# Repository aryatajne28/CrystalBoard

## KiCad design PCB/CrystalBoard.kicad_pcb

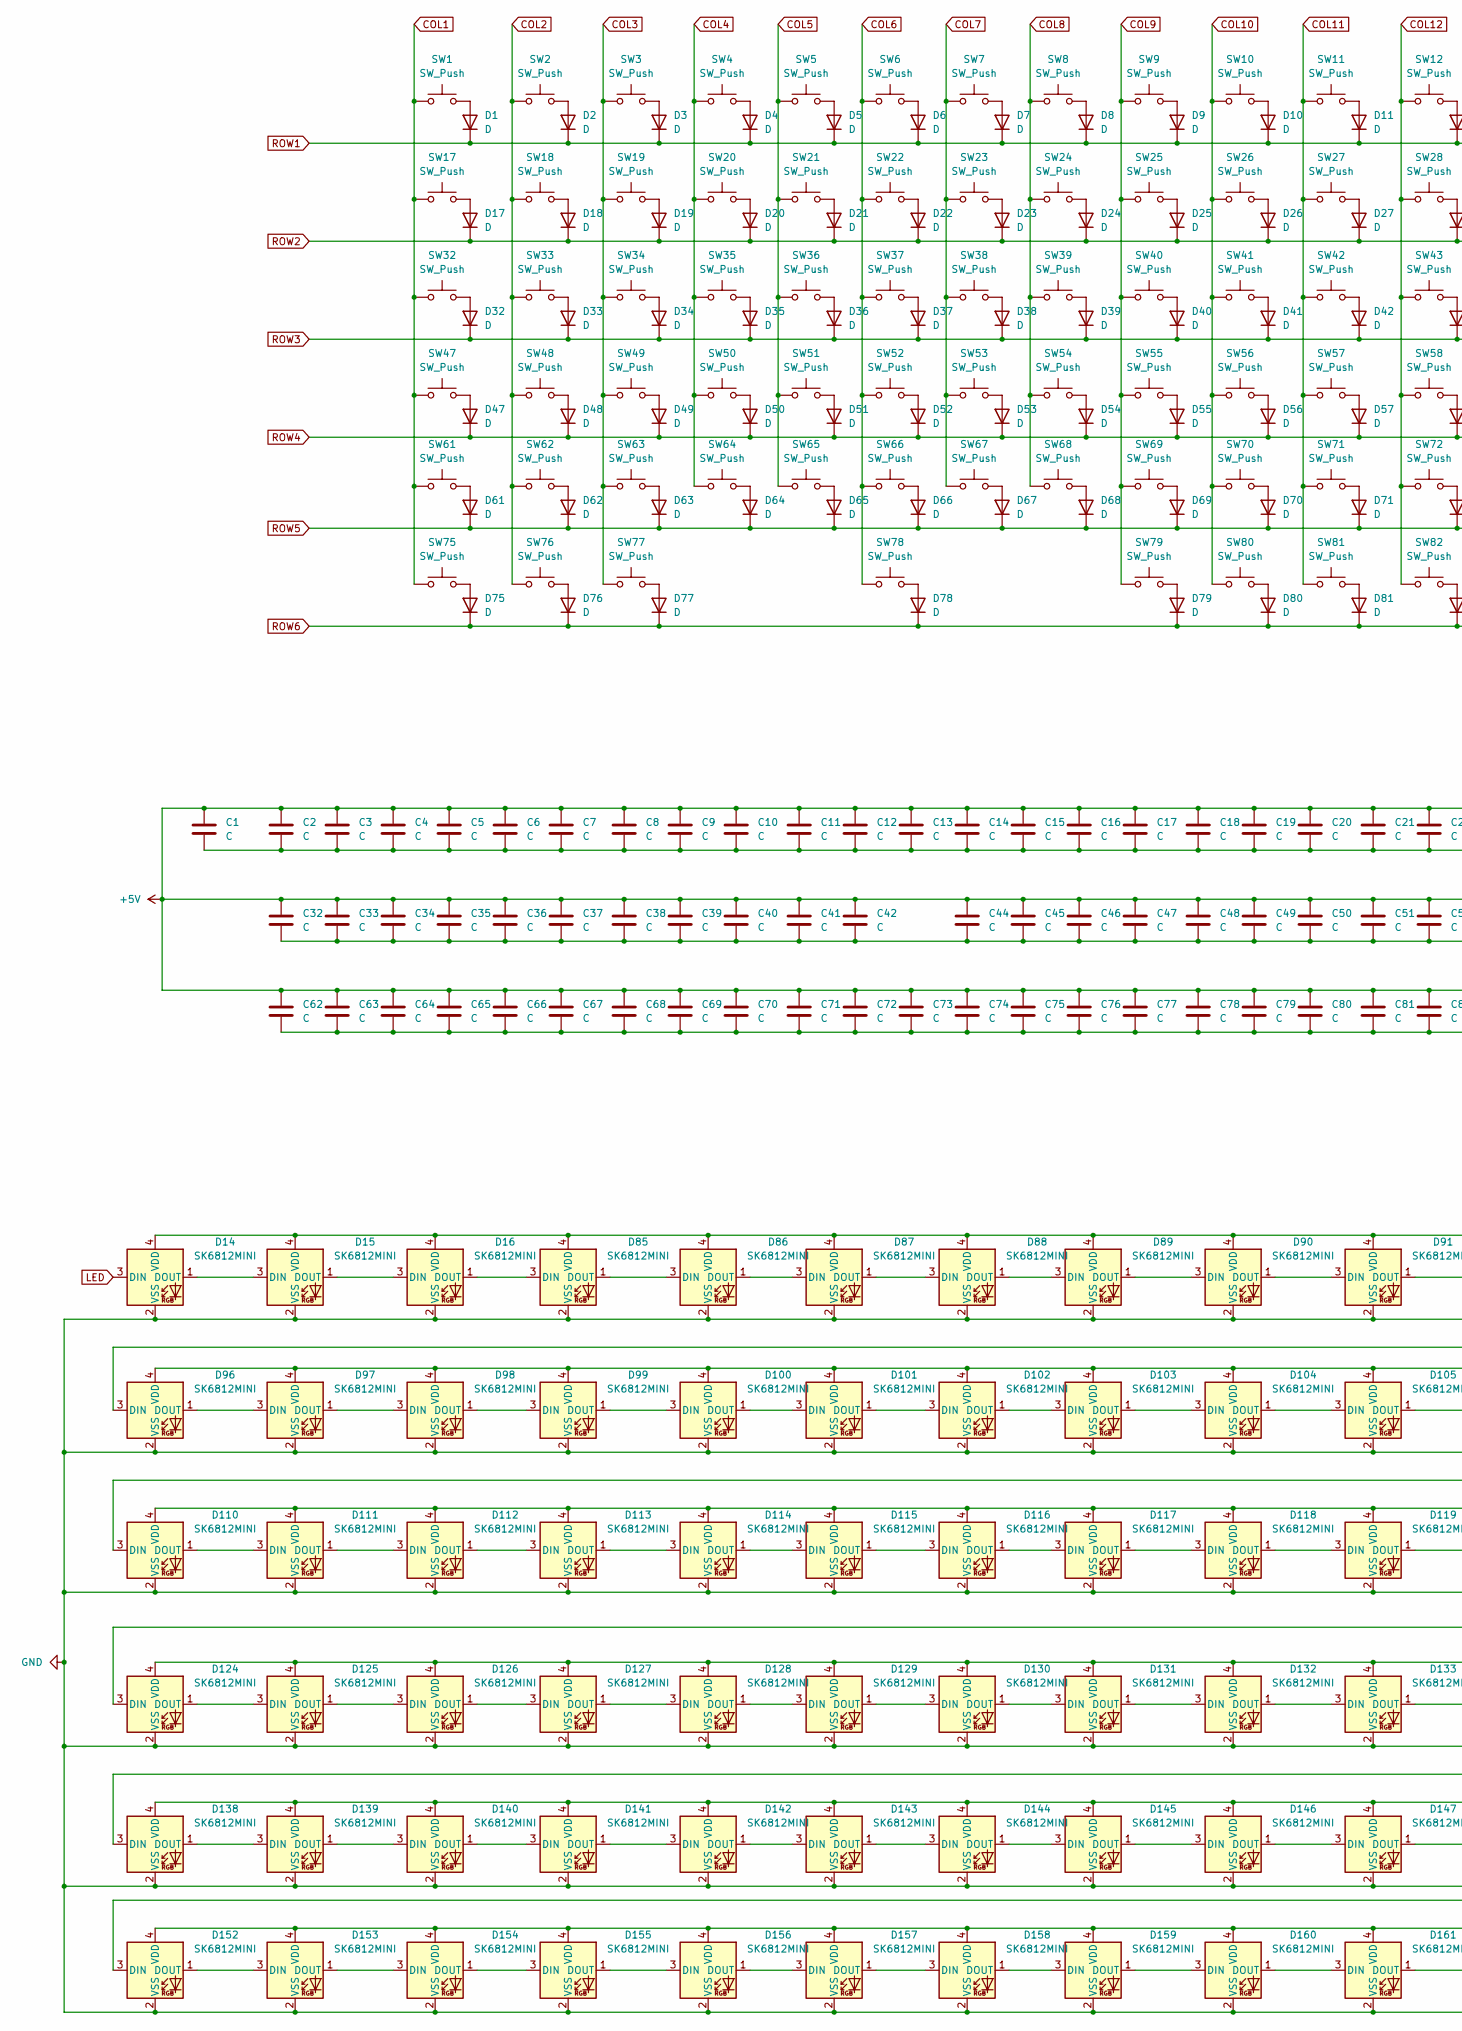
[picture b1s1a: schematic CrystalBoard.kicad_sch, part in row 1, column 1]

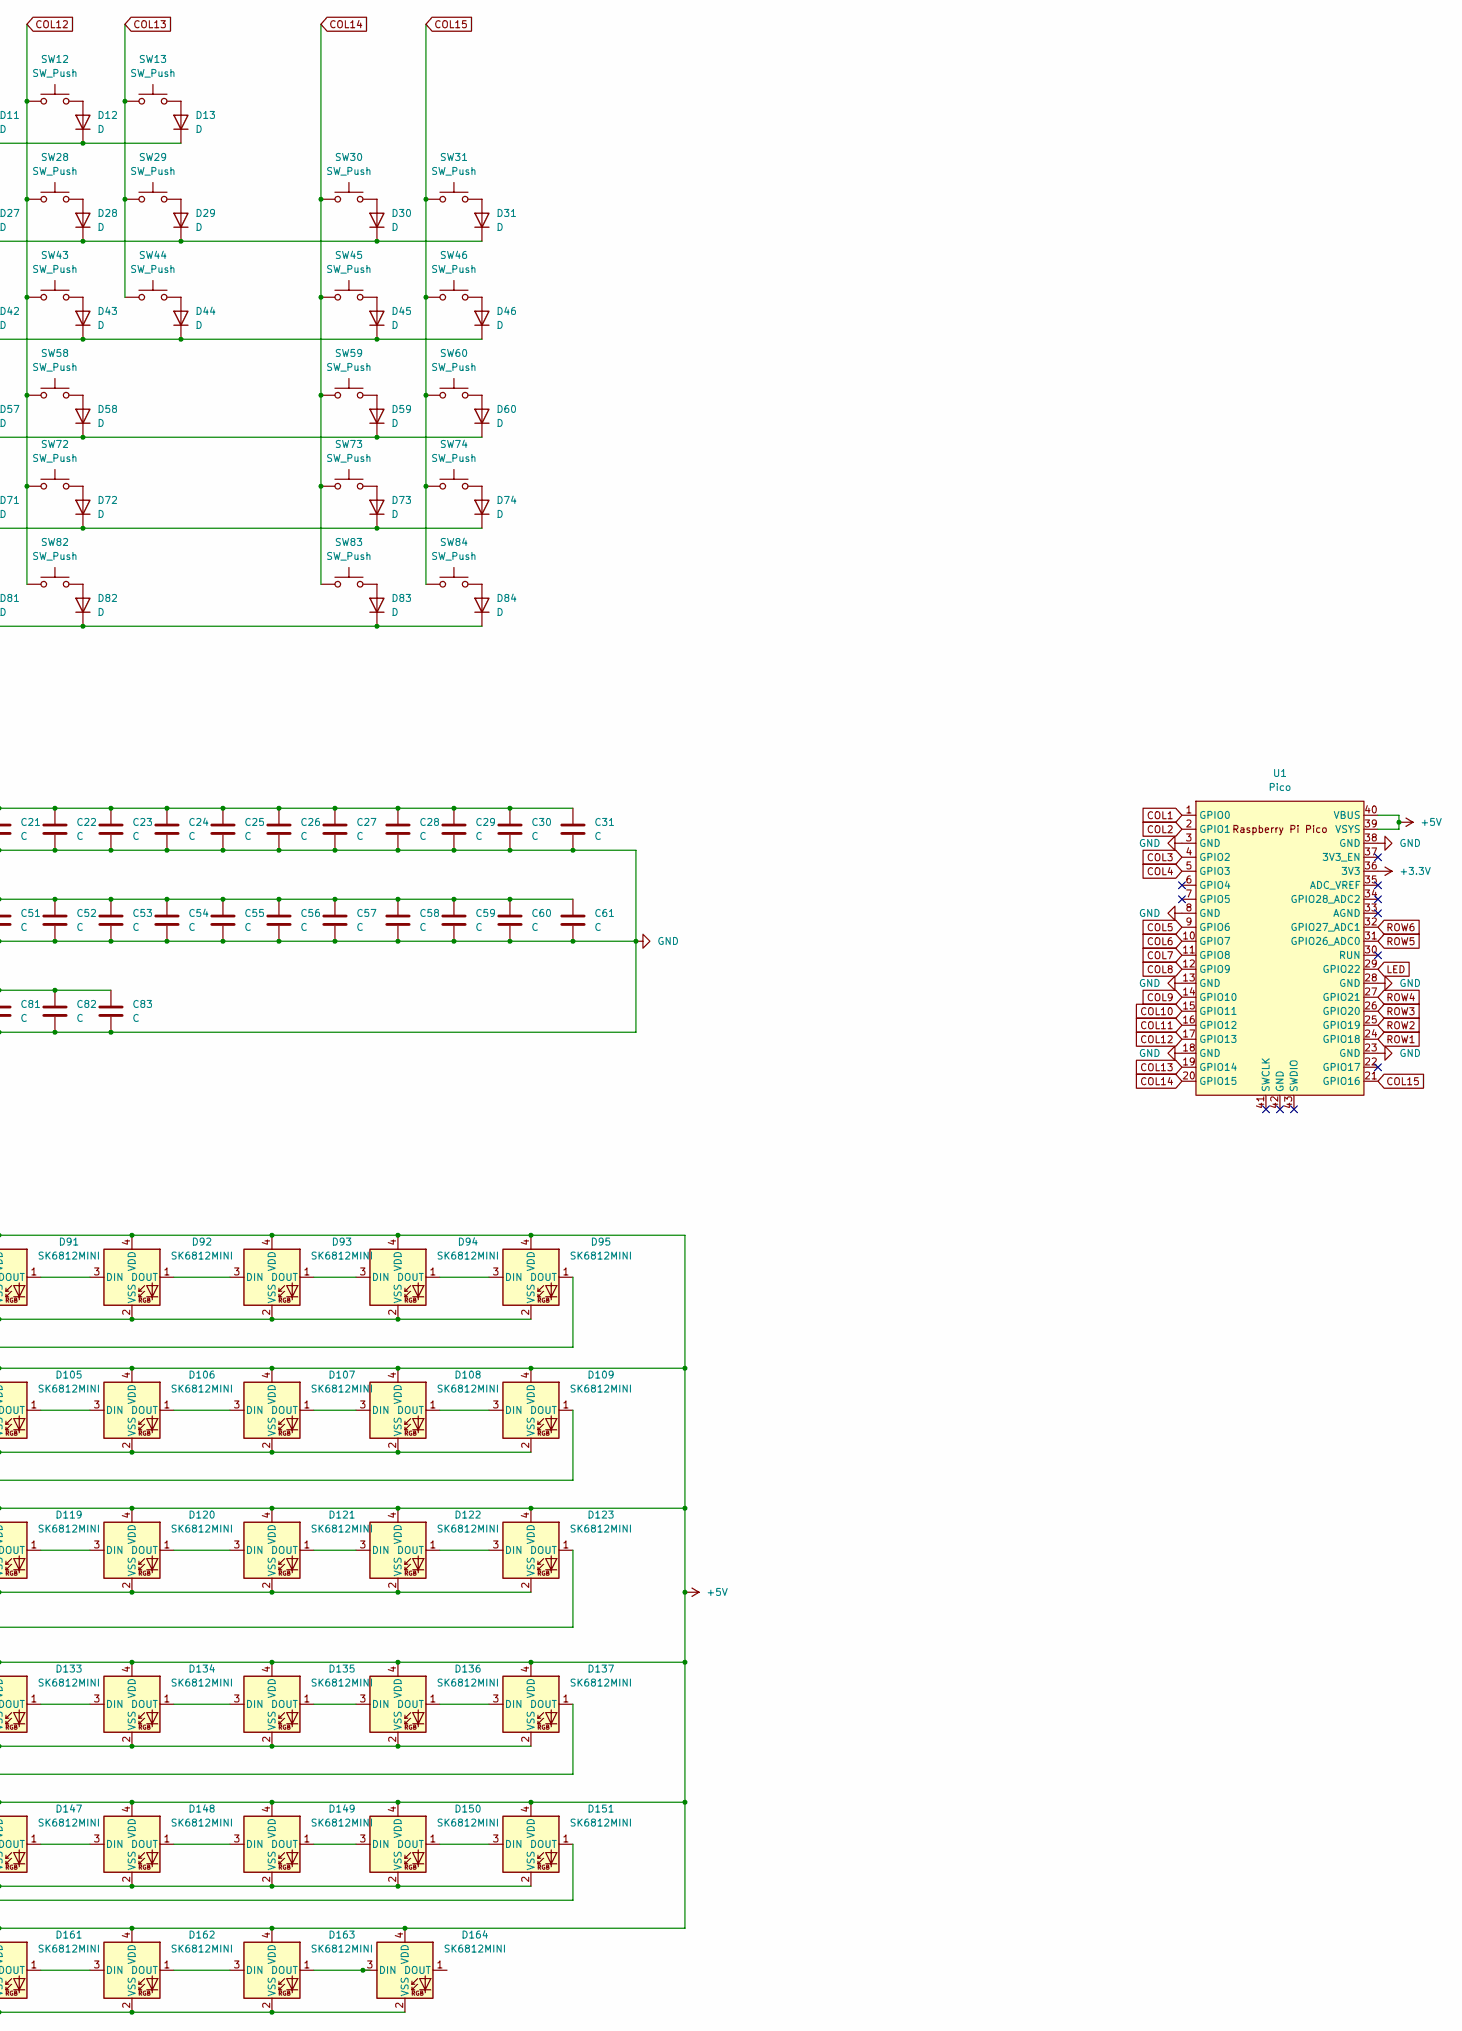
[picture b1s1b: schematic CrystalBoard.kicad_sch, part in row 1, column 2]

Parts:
C1, C2, C3, C4, C5, C6, C7, C8, C9, C10, C11, C12, C13, C14, C15, C16, C17, C18, C19, C20, C21, C22, C23, C24, C25, C26, C27, C28, C29, C30, C31, C32, C33, C34, C35, C36, C37, C38, C39, C40, C41, C42, C44, C45, C46, C47, C48, C49, C50, C51, C52, C53, C54, C55, C56, C57, C58, C59, C60, C61, C62, C63, C64, C65, C66, C67, C68, C69, C70, C71, C72, C73, C74, C75, C76, C77, C78, C79, C80, C81, C82, C83: C; C_0805_2012Metric_Pad1.18x1.45mm_HandSolder
D1, D2, D3, D4, D5, D6, D7, D8, D9, D10, D11, D12, D13, D17, D18, D19, D20, D21, D22, D23, D24, D25, D26, D27, D28, D29, D30, D31, D32, D33, D34, D35, D36, D37, D38, D39, D40, D41, D42, D43, D44, D45, D46, D47, D48, D49, D50, D51, D52, D53, D54, D55, D56, D57, D58, D59, D60, D61, D62, D63, D64, D65, D66, D67, D68, D69, D70, D71, D72, D73, D74, D75, D76, D77, D78, D79, D80, D81, D82, D83, D84: D; D_DO-35_SOD27_P7.62mm_Horizontal
D14, D15, D16, D85, D86, D87, D88, D89, D90, D91, D92, D93, D94, D95, D96, D97, D98, D99, D100, D101, D102, D103, D104, D105, D106, D107, D108, D109, D110, D111, D112, D113, D114, D115, D116, D117, D118, D119, D120, D121, D122, D123, D124, D125, D126, D127, D128, D129, D130, D131, D132, D133, D134, D135, D136, D137, D138, D139, D140, D141, D142, D143, D144, D145, D146, D147, D148, D149, D150, D151, D152, D153, D154, D155, D156, D157, D158, D159, D160, D161, D162, D163, D164: SK6812MINI; SK6812-MINI-E
SW1, SW2, SW3, SW4, SW5, SW6, SW7, SW8, SW9, SW10, SW11, SW12, SW13, SW17, SW18, SW19, SW20, SW21, SW22, SW23, SW24, SW25, SW26, SW27, SW28, SW29, SW31, SW33, SW34, SW35, SW36, SW37, SW38, SW39, SW40, SW41, SW42, SW43, SW44, SW46, SW48, SW49, SW50, SW51, SW52, SW53, SW54, SW55, SW56, SW57, SW58, SW60, SW62, SW63, SW64, SW65, SW66, SW67, SW68, SW69, SW70, SW71, SW73, SW74, SW79, SW80, SW81, SW82, SW83, SW84: SW_Push; SW_Cherry_MX_PCB_1.00u
SW30: SW_Push; SW_Cherry_MX_PCB_2.00u
SW32, SW45: SW_Push; SW_Cherry_MX_PCB_1.50u
SW47, SW72: SW_Push; SW_Cherry_MX_PCB_1.75u
SW59, SW61: SW_Push; SW_Cherry_MX_PCB_2.25u
SW75, SW76, SW77: SW_Push; SW_Cherry_MX_PCB_1.25u
SW78: SW_Push; SW_Cherry_MX_PCB_6.25u
U1: Pico; RPi_Pico_SMD_TH

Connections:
+3.3V: U1.36 (3V3)
+5V: C1.1, C2.1, C3.1, C4.1, C5.1, C6.1, C7.1, C8.1, C9.1, C10.1, C11.1, C12.1, C13.1, C14.1, C15.1, C16.1, C17.1, C18.1, C19.1, C20.1, C21.1, C22.1, C23.1, C24.1, C25.1, C26.1, C27.1, C28.1, C29.1, C30.1, C31.1, C32.1, C33.1, C34.1, C35.1, C36.1, C37.1, C38.1, C39.1, C40.1, C41.1, C42.1, C44.1, C45.1, C46.1, C47.1, C48.1, C49.1, C50.1, C51.1, C52.1, C53.1, C54.1, C55.1, C56.1, C57.1, C58.1, C59.1, C60.1, C61.1, C62.1, C63.1, C64.1, C65.1, C66.1, C67.1, C68.1, C69.1, C70.1, C71.1, C72.1, C73.1, C74.1, C75.1, C76.1, C77.1, C78.1, C79.1, C80.1, C81.1, C82.1, C83.1, D14.4 (VDD), D15.4 (VDD), D16.4 (VDD), D85.4 (VDD), D86.4 (VDD), D87.4 (VDD), D88.4 (VDD), D89.4 (VDD), D90.4 (VDD), D91.4 (VDD), D92.4 (VDD), D93.4 (VDD), D94.4 (VDD), D95.4 (VDD), D96.4 (VDD), D97.4 (VDD), D98.4 (VDD), D99.4 (VDD), D100.4 (VDD), D101.4 (VDD), D102.4 (VDD), D103.4 (VDD), D104.4 (VDD), D105.4 (VDD), D106.4 (VDD), D107.4 (VDD), D108.4 (VDD), D109.4 (VDD), D110.4 (VDD), D111.4 (VDD), D112.4 (VDD), D113.4 (VDD), D114.4 (VDD), D115.4 (VDD), D116.4 (VDD), D117.4 (VDD), D118.4 (VDD), D119.4 (VDD), D120.4 (VDD), D121.4 (VDD), D122.4 (VDD), D123.4 (VDD), D124.4 (VDD), D125.4 (VDD), D126.4 (VDD), D127.4 (VDD), D128.4 (VDD), D129.4 (VDD), D130.4 (VDD), D131.4 (VDD), D132.4 (VDD), D133.4 (VDD), D134.4 (VDD), D135.4 (VDD), D136.4 (VDD), D137.4 (VDD), D138.4 (VDD), D139.4 (VDD), D140.4 (VDD), D141.4 (VDD), D142.4 (VDD), D143.4 (VDD), D144.4 (VDD), D145.4 (VDD), D146.4 (VDD), D147.4 (VDD), D148.4 (VDD), D149.4 (VDD), D150.4 (VDD), D151.4 (VDD), D152.4 (VDD), D153.4 (VDD), D154.4 (VDD), D155.4 (VDD), D156.4 (VDD), D157.4 (VDD), D158.4 (VDD), D159.4 (VDD), D160.4 (VDD), D161.4 (VDD), D162.4 (VDD), D163.4 (VDD), D164.4 (VDD), U1.39 (VSYS), U1.40 (VBUS); also elsewhere on the board
COL1: SW1.1, SW17.1, SW32.1, SW47.1, SW61.1, SW75.1, U1.1 (GPIO0)
COL2: SW2.1, SW18.1, SW33.1, SW48.1, SW62.1, SW76.1, U1.2 (GPIO1)
COL3: SW3.1, SW19.1, SW34.1, SW49.1, SW63.1, SW77.1, U1.4 (GPIO2)
COL4: SW4.1, SW20.1, SW35.1, SW50.1, SW64.1, U1.5 (GPIO3)
COL5: SW5.1, SW21.1, SW36.1, SW51.1, SW65.1, U1.9 (GPIO6)
COL6: SW6.1, SW22.1, SW37.1, SW52.1, SW66.1, SW78.1, U1.10 (GPIO7)
COL7: SW7.1, SW23.1, SW38.1, SW53.1, SW67.1, U1.11 (GPIO8)
COL8: SW8.1, SW24.1, SW39.1, SW54.1, SW68.1, U1.12 (GPIO9)
COL9: SW9.1, SW25.1, SW40.1, SW55.1, SW69.1, SW79.1, U1.14 (GPIO10)
COL10: SW10.1, SW26.1, SW41.1, SW56.1, SW70.1, SW80.1, U1.15 (GPIO11)
COL11: SW11.1, SW27.1, SW42.1, SW57.1, SW71.1, SW81.1, U1.16 (GPIO12)
COL12: SW12.1, SW28.1, SW43.1, SW58.1, SW72.1, SW82.1, U1.17 (GPIO13)
COL13: SW13.1, SW29.1, SW44.1, U1.19 (GPIO14)
COL14: SW30.1, SW45.1, SW59.1, SW73.1, SW83.1, U1.20 (GPIO15)
COL15: SW31.1, SW46.1, SW60.1, SW74.1, SW84.1, U1.21 (GPIO16)
GND: C1.2, C2.2, C3.2, C4.2, C5.2, C6.2, C7.2, C8.2, C9.2, C10.2, C11.2, C12.2, C13.2, C14.2, C15.2, C16.2, C17.2, C18.2, C19.2, C20.2, C21.2, C22.2, C23.2, C24.2, C25.2, C26.2, C27.2, C28.2, C29.2, C30.2, C31.2, C32.2, C33.2, C34.2, C35.2, C36.2, C37.2, C38.2, C39.2, C40.2, C41.2, C42.2, C44.2, C45.2, C46.2, C47.2, C48.2, C49.2, C50.2, C51.2, C52.2, C53.2, C54.2, C55.2, C56.2, C57.2, C58.2, C59.2, C60.2, C61.2, C62.2, C63.2, C64.2, C65.2, C66.2, C67.2, C68.2, C69.2, C70.2, C71.2, C72.2, C73.2, C74.2, C75.2, C76.2, C77.2, C78.2, C79.2, C80.2, C81.2, C82.2, C83.2, D14.2 (VSS), D15.2 (VSS), D16.2 (VSS), D85.2 (VSS), D86.2 (VSS), D87.2 (VSS), D88.2 (VSS), D89.2 (VSS), D90.2 (VSS), D91.2 (VSS), D92.2 (VSS), D93.2 (VSS), D94.2 (VSS), D95.2 (VSS), D96.2 (VSS), D97.2 (VSS), D98.2 (VSS), D99.2 (VSS), D100.2 (VSS), D101.2 (VSS), D102.2 (VSS), D103.2 (VSS), D104.2 (VSS), D105.2 (VSS), D106.2 (VSS), D107.2 (VSS), D108.2 (VSS), D109.2 (VSS), D110.2 (VSS), D111.2 (VSS), D112.2 (VSS), D113.2 (VSS), D114.2 (VSS), D115.2 (VSS), D116.2 (VSS), D117.2 (VSS), D118.2 (VSS), D119.2 (VSS), D120.2 (VSS), D121.2 (VSS), D122.2 (VSS), D123.2 (VSS), D124.2 (VSS), D125.2 (VSS), D126.2 (VSS), D127.2 (VSS), D128.2 (VSS), D129.2 (VSS), D130.2 (VSS), D131.2 (VSS), D132.2 (VSS), D133.2 (VSS), D134.2 (VSS), D135.2 (VSS), D136.2 (VSS), D137.2 (VSS), D138.2 (VSS), D139.2 (VSS), D140.2 (VSS), D141.2 (VSS), D142.2 (VSS), D143.2 (VSS), D144.2 (VSS), D145.2 (VSS), D146.2 (VSS), D147.2 (VSS), D148.2 (VSS), D149.2 (VSS), D150.2 (VSS), D151.2 (VSS), D152.2 (VSS), D153.2 (VSS), D154.2 (VSS), D155.2 (VSS), D156.2 (VSS), D157.2 (VSS), D158.2 (VSS), D159.2 (VSS), D160.2 (VSS), D161.2 (VSS), D162.2 (VSS), D163.2 (VSS), D164.2 (VSS), U1.3 (GND), U1.8 (GND), U1.13 (GND), U1.18 (GND), U1.23 (GND), U1.28 (GND), U1.38 (GND); also elsewhere on the board
LED: D14.3 (DIN), U1.29 (GPIO22)
unnamed: D1.2 (A), SW1.2
unnamed: D2.2 (A), SW2.2
unnamed: D3.2 (A), SW3.2
unnamed: D4.2 (A), SW4.2
unnamed: D5.2 (A), SW5.2
unnamed: D6.2 (A), SW6.2
unnamed: D7.2 (A), SW7.2
unnamed: D8.2 (A), SW8.2
unnamed: D9.2 (A), SW9.2
unnamed: D10.2 (A), SW10.2
unnamed: D11.2 (A), SW11.2
unnamed: D12.2 (A), SW12.2
unnamed: D13.2 (A), SW13.2
unnamed: D14.1 (DOUT), D15.3 (DIN)
unnamed: D15.1 (DOUT), D16.3 (DIN)
unnamed: D16.1 (DOUT), D85.3 (DIN)
unnamed: D17.2 (A), SW17.2
unnamed: D18.2 (A), SW18.2
unnamed: D19.2 (A), SW19.2
unnamed: D20.2 (A), SW20.2
unnamed: D21.2 (A), SW21.2
unnamed: D22.2 (A), SW22.2
unnamed: D23.2 (A), SW23.2
unnamed: D24.2 (A), SW24.2
unnamed: D25.2 (A), SW25.2
unnamed: D26.2 (A), SW26.2
unnamed: D27.2 (A), SW27.2
unnamed: D28.2 (A), SW28.2
unnamed: D29.2 (A), SW29.2
unnamed: D30.2 (A), SW30.2
unnamed: D31.2 (A), SW31.2
unnamed: D32.2 (A), SW32.2
unnamed: D33.2 (A), SW33.2
unnamed: D34.2 (A), SW34.2
unnamed: D35.2 (A), SW35.2
unnamed: D36.2 (A), SW36.2
unnamed: D37.2 (A), SW37.2
unnamed: D38.2 (A), SW38.2
unnamed: D39.2 (A), SW39.2
unnamed: D40.2 (A), SW40.2
unnamed: D41.2 (A), SW41.2
unnamed: D42.2 (A), SW42.2
unnamed: D43.2 (A), SW43.2
unnamed: D44.2 (A), SW44.2
unnamed: D45.2 (A), SW45.2
unnamed: D46.2 (A), SW46.2
unnamed: D47.2 (A), SW47.2
unnamed: D48.2 (A), SW48.2
unnamed: D49.2 (A), SW49.2
unnamed: D50.2 (A), SW50.2
unnamed: D51.2 (A), SW51.2
unnamed: D52.2 (A), SW52.2
unnamed: D53.2 (A), SW53.2
unnamed: D54.2 (A), SW54.2
unnamed: D55.2 (A), SW55.2
unnamed: D56.2 (A), SW56.2
unnamed: D57.2 (A), SW57.2
unnamed: D58.2 (A), SW58.2
unnamed: D59.2 (A), SW59.2
unnamed: D60.2 (A), SW60.2
unnamed: D61.2 (A), SW61.2
unnamed: D62.2 (A), SW62.2
unnamed: D63.2 (A), SW63.2
unnamed: D64.2 (A), SW64.2
unnamed: D65.2 (A), SW65.2
unnamed: D66.2 (A), SW66.2
unnamed: D67.2 (A), SW67.2
unnamed: D68.2 (A), SW68.2
unnamed: D69.2 (A), SW69.2
unnamed: D70.2 (A), SW70.2
unnamed: D71.2 (A), SW71.2
unnamed: D72.2 (A), SW72.2
unnamed: D73.2 (A), SW73.2
unnamed: D74.2 (A), SW74.2
unnamed: D75.2 (A), SW75.2
unnamed: D76.2 (A), SW76.2
unnamed: D77.2 (A), SW77.2
unnamed: D78.2 (A), SW78.2
unnamed: D79.2 (A), SW79.2
unnamed: D80.2 (A), SW80.2
unnamed: D81.2 (A), SW81.2
unnamed: D82.2 (A), SW82.2
unnamed: D83.2 (A), SW83.2
unnamed: D84.2 (A), SW84.2
unnamed: D85.1 (DOUT), D86.3 (DIN)
unnamed: D86.1 (DOUT), D87.3 (DIN)
unnamed: D87.1 (DOUT), D88.3 (DIN)
unnamed: D88.1 (DOUT), D89.3 (DIN)
unnamed: D89.1 (DOUT), D90.3 (DIN)
unnamed: D90.1 (DOUT), D91.3 (DIN)
unnamed: D91.1 (DOUT), D92.3 (DIN)
unnamed: D92.1 (DOUT), D93.3 (DIN)
unnamed: D93.1 (DOUT), D94.3 (DIN)
unnamed: D94.1 (DOUT), D95.3 (DIN)
unnamed: D95.1 (DOUT), D96.3 (DIN)
unnamed: D96.1 (DOUT), D97.3 (DIN)
unnamed: D97.1 (DOUT), D98.3 (DIN)
unnamed: D98.1 (DOUT), D99.3 (DIN)
unnamed: D99.1 (DOUT), D100.3 (DIN)
unnamed: D100.1 (DOUT), D101.3 (DIN)
unnamed: D101.1 (DOUT), D102.3 (DIN)
unnamed: D102.1 (DOUT), D103.3 (DIN)
unnamed: D103.1 (DOUT), D104.3 (DIN)
unnamed: D104.1 (DOUT), D105.3 (DIN)
unnamed: D105.1 (DOUT), D106.3 (DIN)
unnamed: D106.1 (DOUT), D107.3 (DIN)
unnamed: D107.1 (DOUT), D108.3 (DIN)
unnamed: D108.1 (DOUT), D109.3 (DIN)
unnamed: D109.1 (DOUT), D110.3 (DIN)
unnamed: D110.1 (DOUT), D111.3 (DIN)
unnamed: D111.1 (DOUT), D112.3 (DIN)
unnamed: D112.1 (DOUT), D113.3 (DIN)
unnamed: D113.1 (DOUT), D114.3 (DIN)
unnamed: D114.1 (DOUT), D115.3 (DIN)
unnamed: D115.1 (DOUT), D116.3 (DIN)
unnamed: D116.1 (DOUT), D117.3 (DIN)
unnamed: D117.1 (DOUT), D118.3 (DIN)
unnamed: D118.1 (DOUT), D119.3 (DIN)
unnamed: D119.1 (DOUT), D120.3 (DIN)
unnamed: D120.1 (DOUT), D121.3 (DIN)
unnamed: D121.1 (DOUT), D122.3 (DIN)
unnamed: D122.1 (DOUT), D123.3 (DIN)
unnamed: D123.1 (DOUT), D124.3 (DIN)
unnamed: D124.1 (DOUT), D125.3 (DIN)
unnamed: D125.1 (DOUT), D126.3 (DIN)
unnamed: D126.1 (DOUT), D127.3 (DIN)
unnamed: D127.1 (DOUT), D128.3 (DIN)
unnamed: D128.1 (DOUT), D129.3 (DIN)
unnamed: D129.1 (DOUT), D130.3 (DIN)
unnamed: D130.1 (DOUT), D131.3 (DIN)
unnamed: D131.1 (DOUT), D132.3 (DIN)
unnamed: D132.1 (DOUT), D133.3 (DIN)
unnamed: D133.1 (DOUT), D134.3 (DIN)
unnamed: D134.1 (DOUT), D135.3 (DIN)
unnamed: D135.1 (DOUT), D136.3 (DIN)
unnamed: D136.1 (DOUT), D137.3 (DIN)
unnamed: D137.1 (DOUT), D138.3 (DIN)
unnamed: D138.1 (DOUT), D139.3 (DIN)
unnamed: D139.1 (DOUT), D140.3 (DIN)
unnamed: D140.1 (DOUT), D141.3 (DIN)
unnamed: D141.1 (DOUT), D142.3 (DIN)
unnamed: D142.1 (DOUT), D143.3 (DIN)
unnamed: D143.1 (DOUT), D144.3 (DIN)
unnamed: D144.1 (DOUT), D145.3 (DIN)
unnamed: D145.1 (DOUT), D146.3 (DIN)
unnamed: D146.1 (DOUT), D147.3 (DIN)
unnamed: D147.1 (DOUT), D148.3 (DIN)
unnamed: D148.1 (DOUT), D149.3 (DIN)
unnamed: D149.1 (DOUT), D150.3 (DIN)
unnamed: D150.1 (DOUT), D151.3 (DIN)
unnamed: D151.1 (DOUT), D152.3 (DIN)
unnamed: D152.1 (DOUT), D153.3 (DIN)
unnamed: D153.1 (DOUT), D154.3 (DIN)
unnamed: D154.1 (DOUT), D155.3 (DIN)
unnamed: D155.1 (DOUT), D156.3 (DIN)
unnamed: D156.1 (DOUT), D157.3 (DIN)
unnamed: D157.1 (DOUT), D158.3 (DIN)
unnamed: D158.1 (DOUT), D159.3 (DIN)
unnamed: D159.1 (DOUT), D160.3 (DIN)
unnamed: D160.1 (DOUT), D161.3 (DIN)
unnamed: D161.1 (DOUT), D162.3 (DIN)
unnamed: D162.1 (DOUT), D163.3 (DIN)
unnamed: D163.1 (DOUT), D164.3 (DIN)
ROW1: D1.1 (K), D2.1 (K), D3.1 (K), D4.1 (K), D5.1 (K), D6.1 (K), D7.1 (K), D8.1 (K), D9.1 (K), D10.1 (K), D11.1 (K), D12.1 (K), D13.1 (K), U1.24 (GPIO18)
ROW2: D17.1 (K), D18.1 (K), D19.1 (K), D20.1 (K), D21.1 (K), D22.1 (K), D23.1 (K), D24.1 (K), D25.1 (K), D26.1 (K), D27.1 (K), D28.1 (K), D29.1 (K), D30.1 (K), D31.1 (K), U1.25 (GPIO19)
ROW3: D32.1 (K), D33.1 (K), D34.1 (K), D35.1 (K), D36.1 (K), D37.1 (K), D38.1 (K), D39.1 (K), D40.1 (K), D41.1 (K), D42.1 (K), D43.1 (K), D44.1 (K), D45.1 (K), D46.1 (K), U1.26 (GPIO20)
ROW4: D47.1 (K), D48.1 (K), D49.1 (K), D50.1 (K), D51.1 (K), D52.1 (K), D53.1 (K), D54.1 (K), D55.1 (K), D56.1 (K), D57.1 (K), D58.1 (K), D59.1 (K), D60.1 (K), U1.27 (GPIO21)
ROW5: D61.1 (K), D62.1 (K), D63.1 (K), D64.1 (K), D65.1 (K), D66.1 (K), D67.1 (K), D68.1 (K), D69.1 (K), D70.1 (K), D71.1 (K), D72.1 (K), D73.1 (K), D74.1 (K), U1.31 (GPIO26_ADC0)
ROW6: D75.1 (K), D76.1 (K), D77.1 (K), D78.1 (K), D79.1 (K), D80.1 (K), D81.1 (K), D82.1 (K), D83.1 (K), D84.1 (K), U1.32 (GPIO27_ADC1)

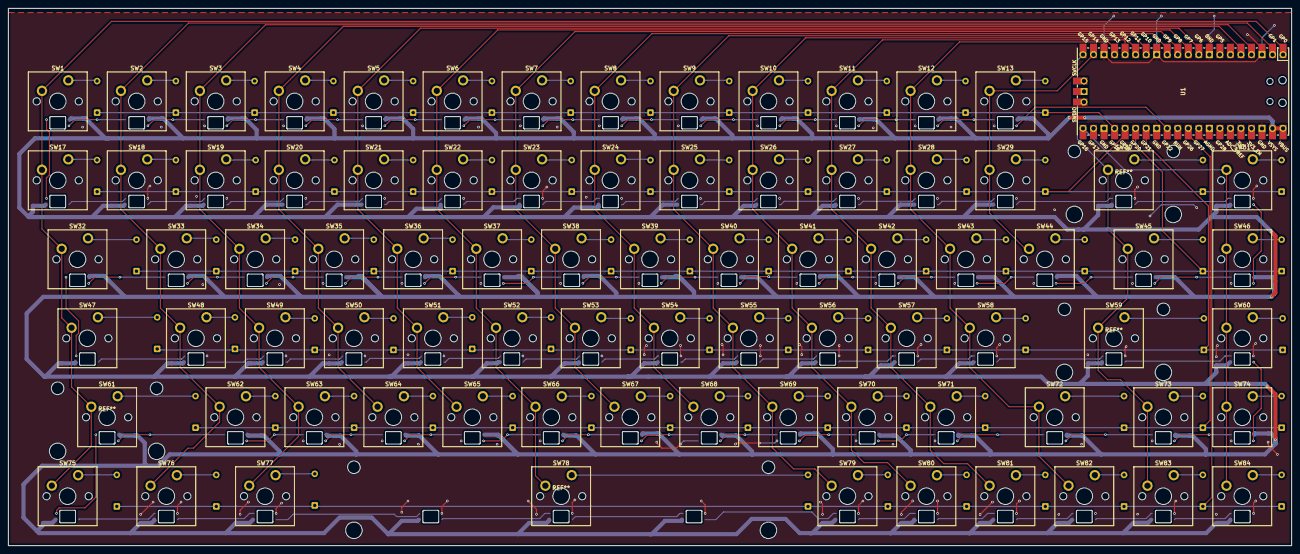
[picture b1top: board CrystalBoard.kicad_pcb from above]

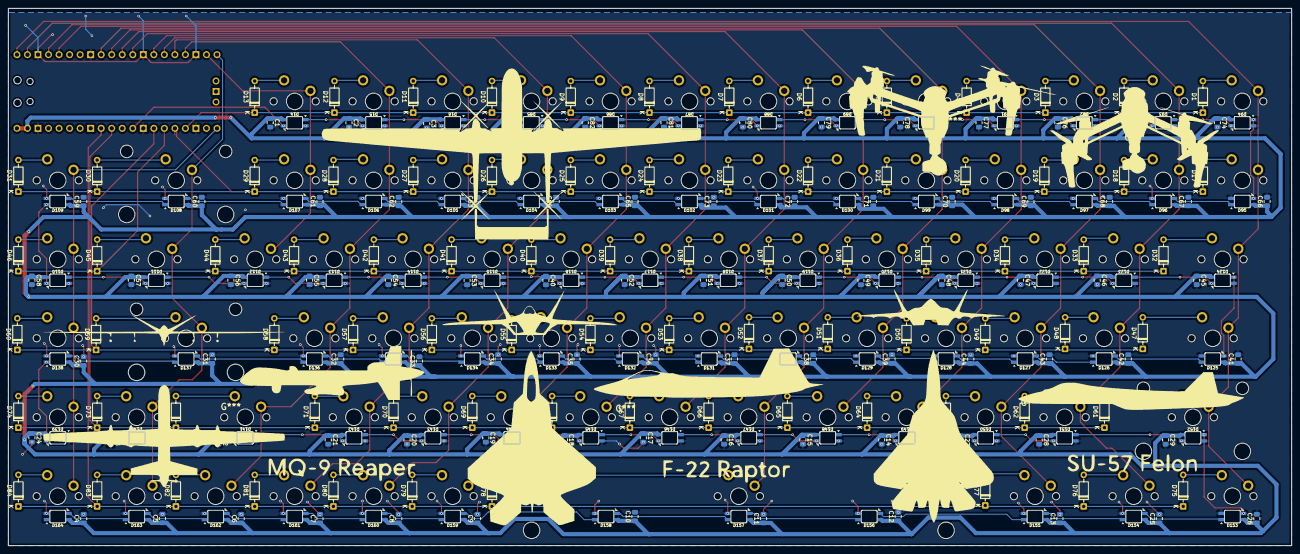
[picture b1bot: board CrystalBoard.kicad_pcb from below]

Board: 2 copper layers, 309.6 x 129.6 mm, 329 parts (247 on the bottom side), 187 nets.

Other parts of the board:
C43: C; C_0805_2012Metric_Pad1.18x1.45mm_HandSolder

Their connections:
+5V: C43.1; also elsewhere on the board
GND: C43.2; also elsewhere on the board

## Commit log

2025-07-26 Added the journal and first work done
2025-07-27 day 2
2025-07-27 day 2 update 2
2025-07-27 day 2 update 3
2025-07-28 Day 3 update 1
2025-07-31 last day updates
2025-07-31 added time spent
2025-07-31 added the firmware code file
2025-07-31 added the dxf files that I made for the Laser cutting of acrylic sheets
2025-07-31 Added the Kicad Project Files
2025-07-31 added the Production Folder with the ZIP folder of PCBs
2025-07-31 added the BOM file
2025-07-31 Final Commit
2025-08-03 changes made according to make it bit more complicated
2025-08-05 Final Update for re-review
2025-08-05 One more Update for re-review
2025-08-12 Re-review 2 by Kai, suggesting to make the Case bit more complex. So implemented a different approach to make the case with a referrence.
2025-08-14 added capacitors to the BOM
2026-04-07 Added the take-two folder!
